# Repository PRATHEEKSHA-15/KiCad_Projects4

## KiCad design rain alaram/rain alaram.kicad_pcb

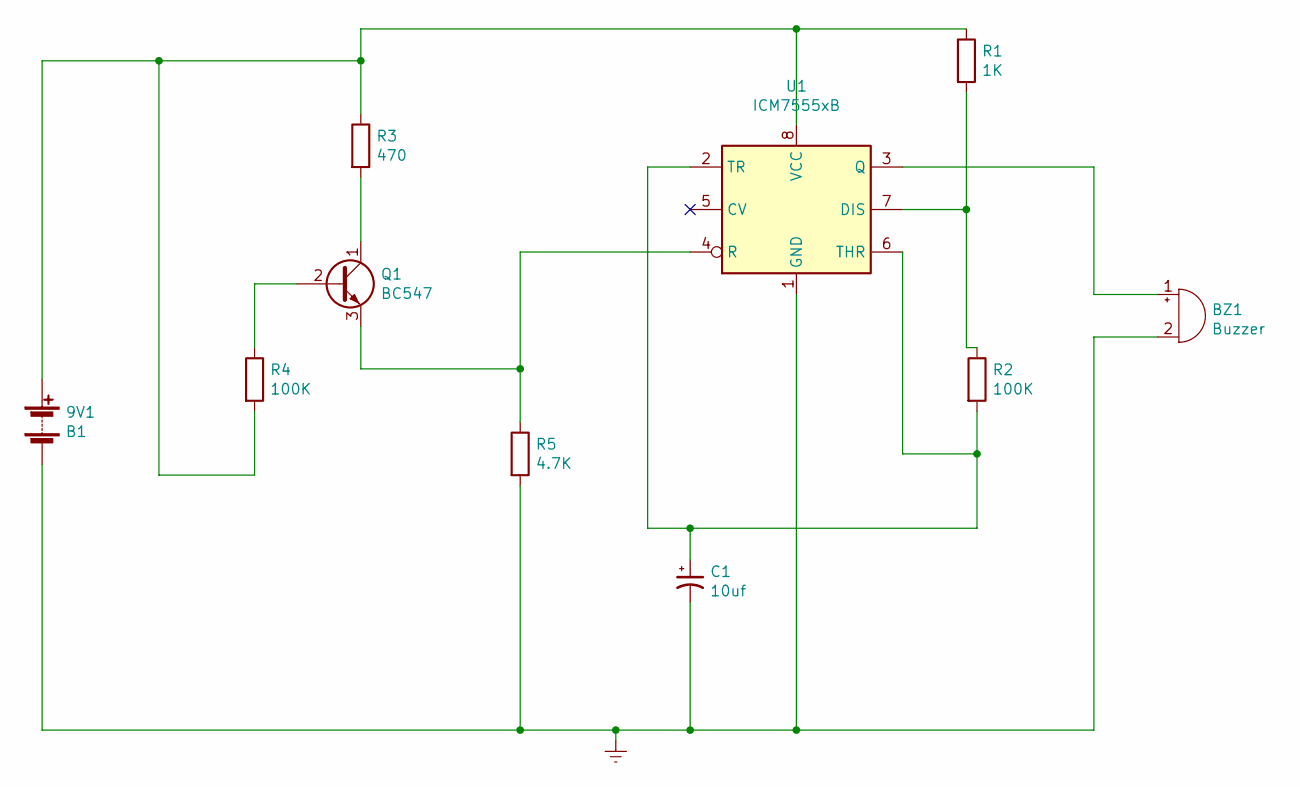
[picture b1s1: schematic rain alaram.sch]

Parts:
9V1: B1; PinHeader_1x02_P2.54mm_Vertical
BZ1: Buzzer; Buzzer_TDK_PS1240P02BT_D12.2mm_H6.5mm
C1: 10uf; CP_Radial_D4.0mm_P2.00mm
Q1: BC547; TO-92_Inline
R1: 1K; R_Axial_DIN0204_L3.6mm_D1.6mm_P5.08mm_Horizontal
R2, R4: 100K; R_Axial_DIN0204_L3.6mm_D1.6mm_P5.08mm_Horizontal
R3: 470; R_Axial_DIN0204_L3.6mm_D1.6mm_P5.08mm_Horizontal
R5: 4.7K; R_Axial_DIN0204_L3.6mm_D1.6mm_P5.08mm_Horizontal
U1: ICM7555xB; SOIC-8_3.9x4.9mm_P1.27mm

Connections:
Earth: 9V1.2 (-), BZ1.2 (+), C1.2, R5.2, U1.1 (GND)
unnamed: 9V1.1 (+), R1.1, R3.1, R4.2, U1.8 (VCC)
unnamed: BZ1.1 (-), U1.3 (Q)
unnamed: C1.1, R2.2, U1.2 (TR), U1.6 (THR)
unnamed: Q1.1 (C), R3.2
unnamed: Q1.2 (B), R4.1
unnamed: Q1.3 (E), R5.1, U1.4 (R)
unnamed: R1.2, R2.1, U1.7 (DIS)

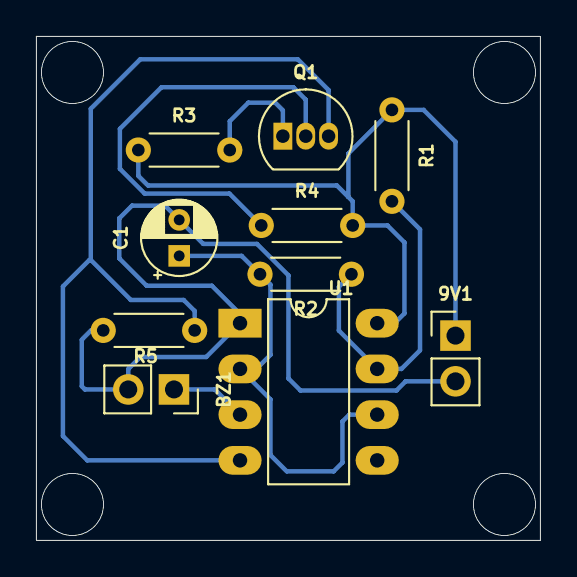
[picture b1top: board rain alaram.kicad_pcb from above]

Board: 2 copper layers, 28.0 x 28.0 mm, 10 parts (0 on the bottom side), 8 nets.

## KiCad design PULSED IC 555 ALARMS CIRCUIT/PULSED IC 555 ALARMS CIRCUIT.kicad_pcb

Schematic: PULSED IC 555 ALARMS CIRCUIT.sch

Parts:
C1: 470uf; C_Disc_D3.0mm_W1.6mm_P2.50mm
C2: 47uf; C_Disc_D3.0mm_W1.6mm_P2.50mm
C3, C4: 0.1; C_Disc_D3.0mm_W1.6mm_P2.50mm
D1: IN4148; D_A-405_P2.54mm_Vertical_AnodeUp
D2, D3, D4: IN4001; D_A-405_P2.54mm_Vertical_AnodeUp
LS1: 8ohm; PinSocket_1x02_P2.54mm_Vertical
Q1: 2N3906; TO-92_Inline
Q2: 2N3704; TO92
Q3: 2N3055; TO-3
R1, R5: 10K; R_Axial_DIN0204_L3.6mm_D1.6mm_P5.08mm_Horizontal
R2: 33K; R_Axial_DIN0204_L3.6mm_D1.6mm_P5.08mm_Horizontal
R3: 12K; R_Axial_DIN0204_L3.6mm_D1.6mm_P5.08mm_Horizontal
R4: 4.7K; R_Axial_DIN0204_L3.6mm_D1.6mm_P5.08mm_Horizontal
R6: 100K; R_Axial_DIN0204_L3.6mm_D1.6mm_P5.08mm_Horizontal
R7: 2.7K; R_Axial_DIN0204_L3.6mm_D1.6mm_P5.08mm_Horizontal
R8: R; R_Axial_DIN0204_L3.6mm_D1.6mm_P5.08mm_Horizontal
S1: FSM8JH; SW_FSM8JH; PARTREV C10
U1, U2: LM555xM; DIP-8_W7.62mm_LongPads

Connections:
Earth: C1.2, C2.2, C3.2, C4.2, D4.2 (A), Q1.1 (E), Q2.3, Q3.2 (E), S1.3, S1.4, U1.1 (GND), U2.1 (GND); also elsewhere on the board
unnamed: C1.1, D2.1 (K), R1.1, R4.1, R5.1, U1.4 (R), U1.8 (VCC), U2.4 (R), U2.8 (VCC)
unnamed: C2.1, D1.1 (K), Q1.2 (B), R2.2, U1.2 (TR), U1.6 (THR)
unnamed: C3.1, U1.5 (CV)
unnamed: C4.1, Q2.2, R6.2, U2.2 (TR), U2.6 (THR)
unnamed: D1.2 (A), R1.2, R2.1, U1.7 (DIS)
unnamed 6: D2.2 (A), D3.1 (K), LS1.1, S1.1, S1.2; also elsewhere on the board
unnamed: D3.2 (A), D4.1 (K), LS1.2, Q3.3 (C)
unnamed: Q1.3 (C), R4.2, R7.2
unnamed: Q2.1, R3.2
unnamed: Q3.1 (B), R8.2
unnamed: R3.1, U1.3 (Q)
unnamed: R5.2, R6.1, U2.7 (DIS)
unnamed: R7.1, U2.5 (CV)
unnamed: R8.1, U2.3 (Q)

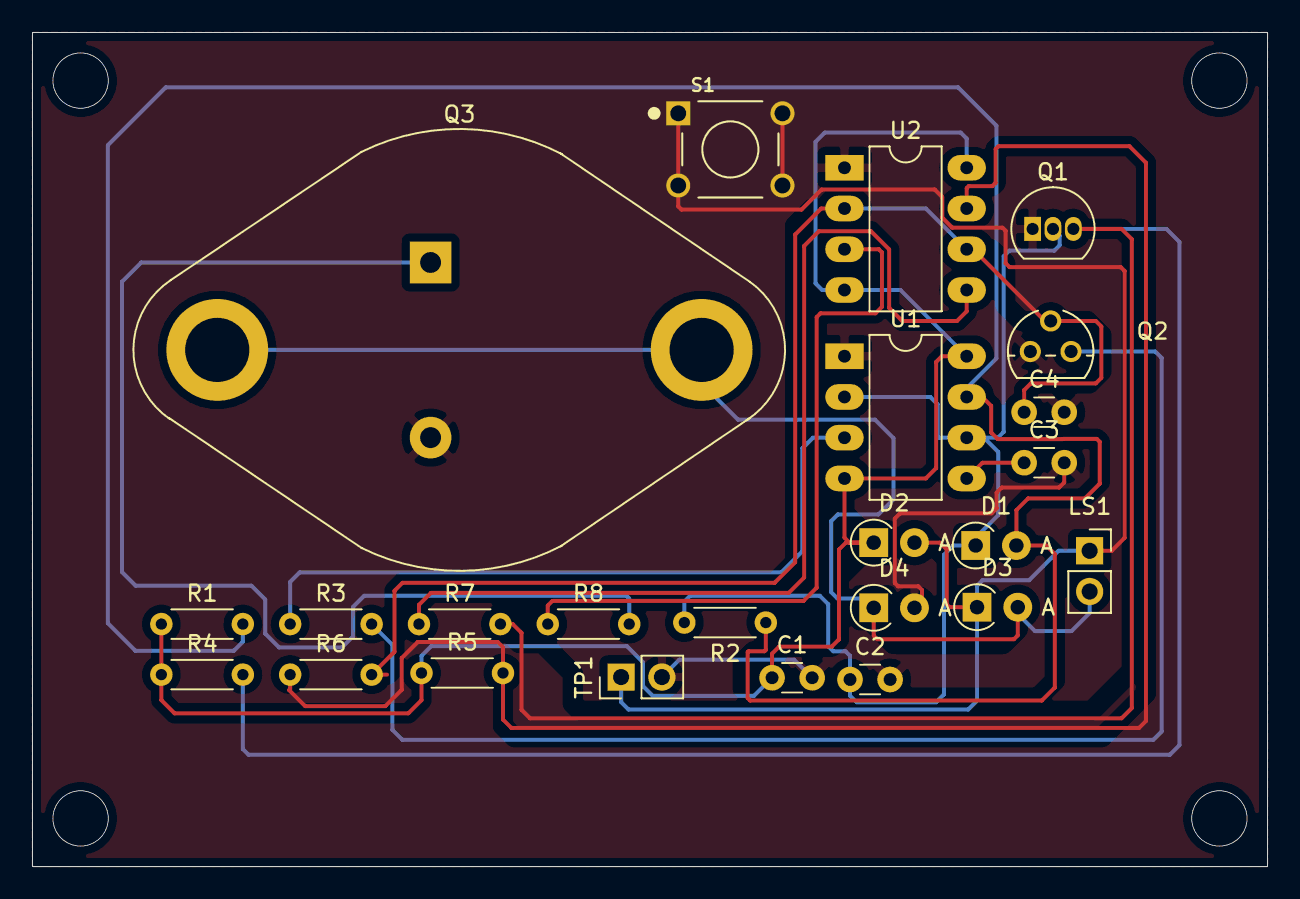
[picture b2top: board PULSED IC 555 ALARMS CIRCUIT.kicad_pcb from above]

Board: 2 copper layers, 77.0 x 52.0 mm, 24 parts (0 on the bottom side), 15 nets.

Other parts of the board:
TP1: 12V OR 15V; PinHeader_1x02_P2.54mm_Vertical

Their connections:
Earth: TP1.2; also elsewhere on the board
unnamed 6: TP1.1; also elsewhere on the board

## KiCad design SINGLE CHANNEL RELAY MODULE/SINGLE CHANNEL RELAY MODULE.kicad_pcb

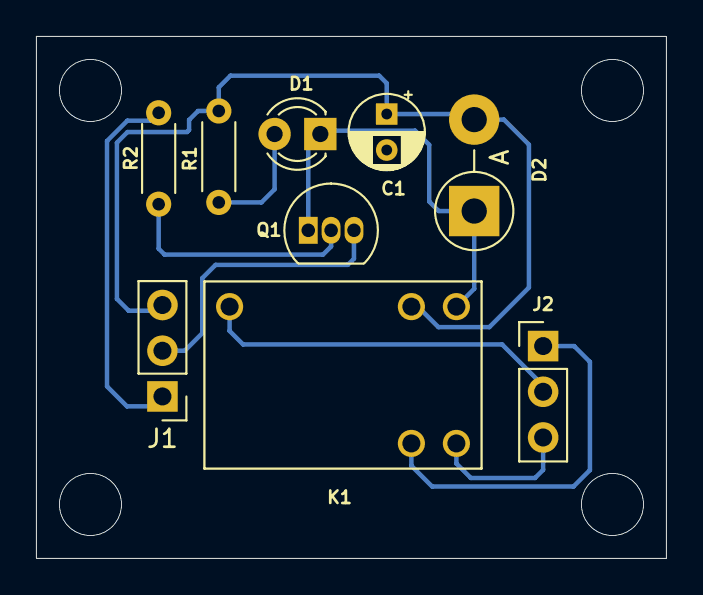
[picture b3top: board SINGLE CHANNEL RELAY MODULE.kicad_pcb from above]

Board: 2 copper layers, 35.0 x 29.0 mm, 9 parts (0 on the bottom side), 9 nets.

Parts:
C1: 0.1uf; CP_Radial_D4.0mm_P2.00mm
D1: LED; LED_D3.0mm
D2: IN4007; D_5W_P5.08mm_Vertical_AnodeUp
J1: conn; PinHeader_1x03_P2.54mm_Vertical
J2: Screw_Terminal; PinHeader_1x03_P2.54mm_Vertical
K1: 6-1419130-5; TE_6-1419130-5
Q1: BC547; TO-92_Inline
R1: 1K; R_Axial_DIN0204_L3.6mm_D1.6mm_P5.08mm_Horizontal
R2: 5.1K; R_Axial_DIN0204_L3.6mm_D1.6mm_P5.08mm_Horizontal

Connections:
Earth: C1.2, J1.2, Q1.3
unnamed: D1.1, D2.1, K1.A1, Q1.1
unnamed: D1.2, R1.2
unnamed: J1.1, R2.2
unnamed: J2.1, K1.14
unnamed: J2.2, K1.11
unnamed: J2.3, K1.12
unnamed: Q1.2, R2.1
VCC: C1.1, D2.2, J1.3, K1.A2, R1.1
